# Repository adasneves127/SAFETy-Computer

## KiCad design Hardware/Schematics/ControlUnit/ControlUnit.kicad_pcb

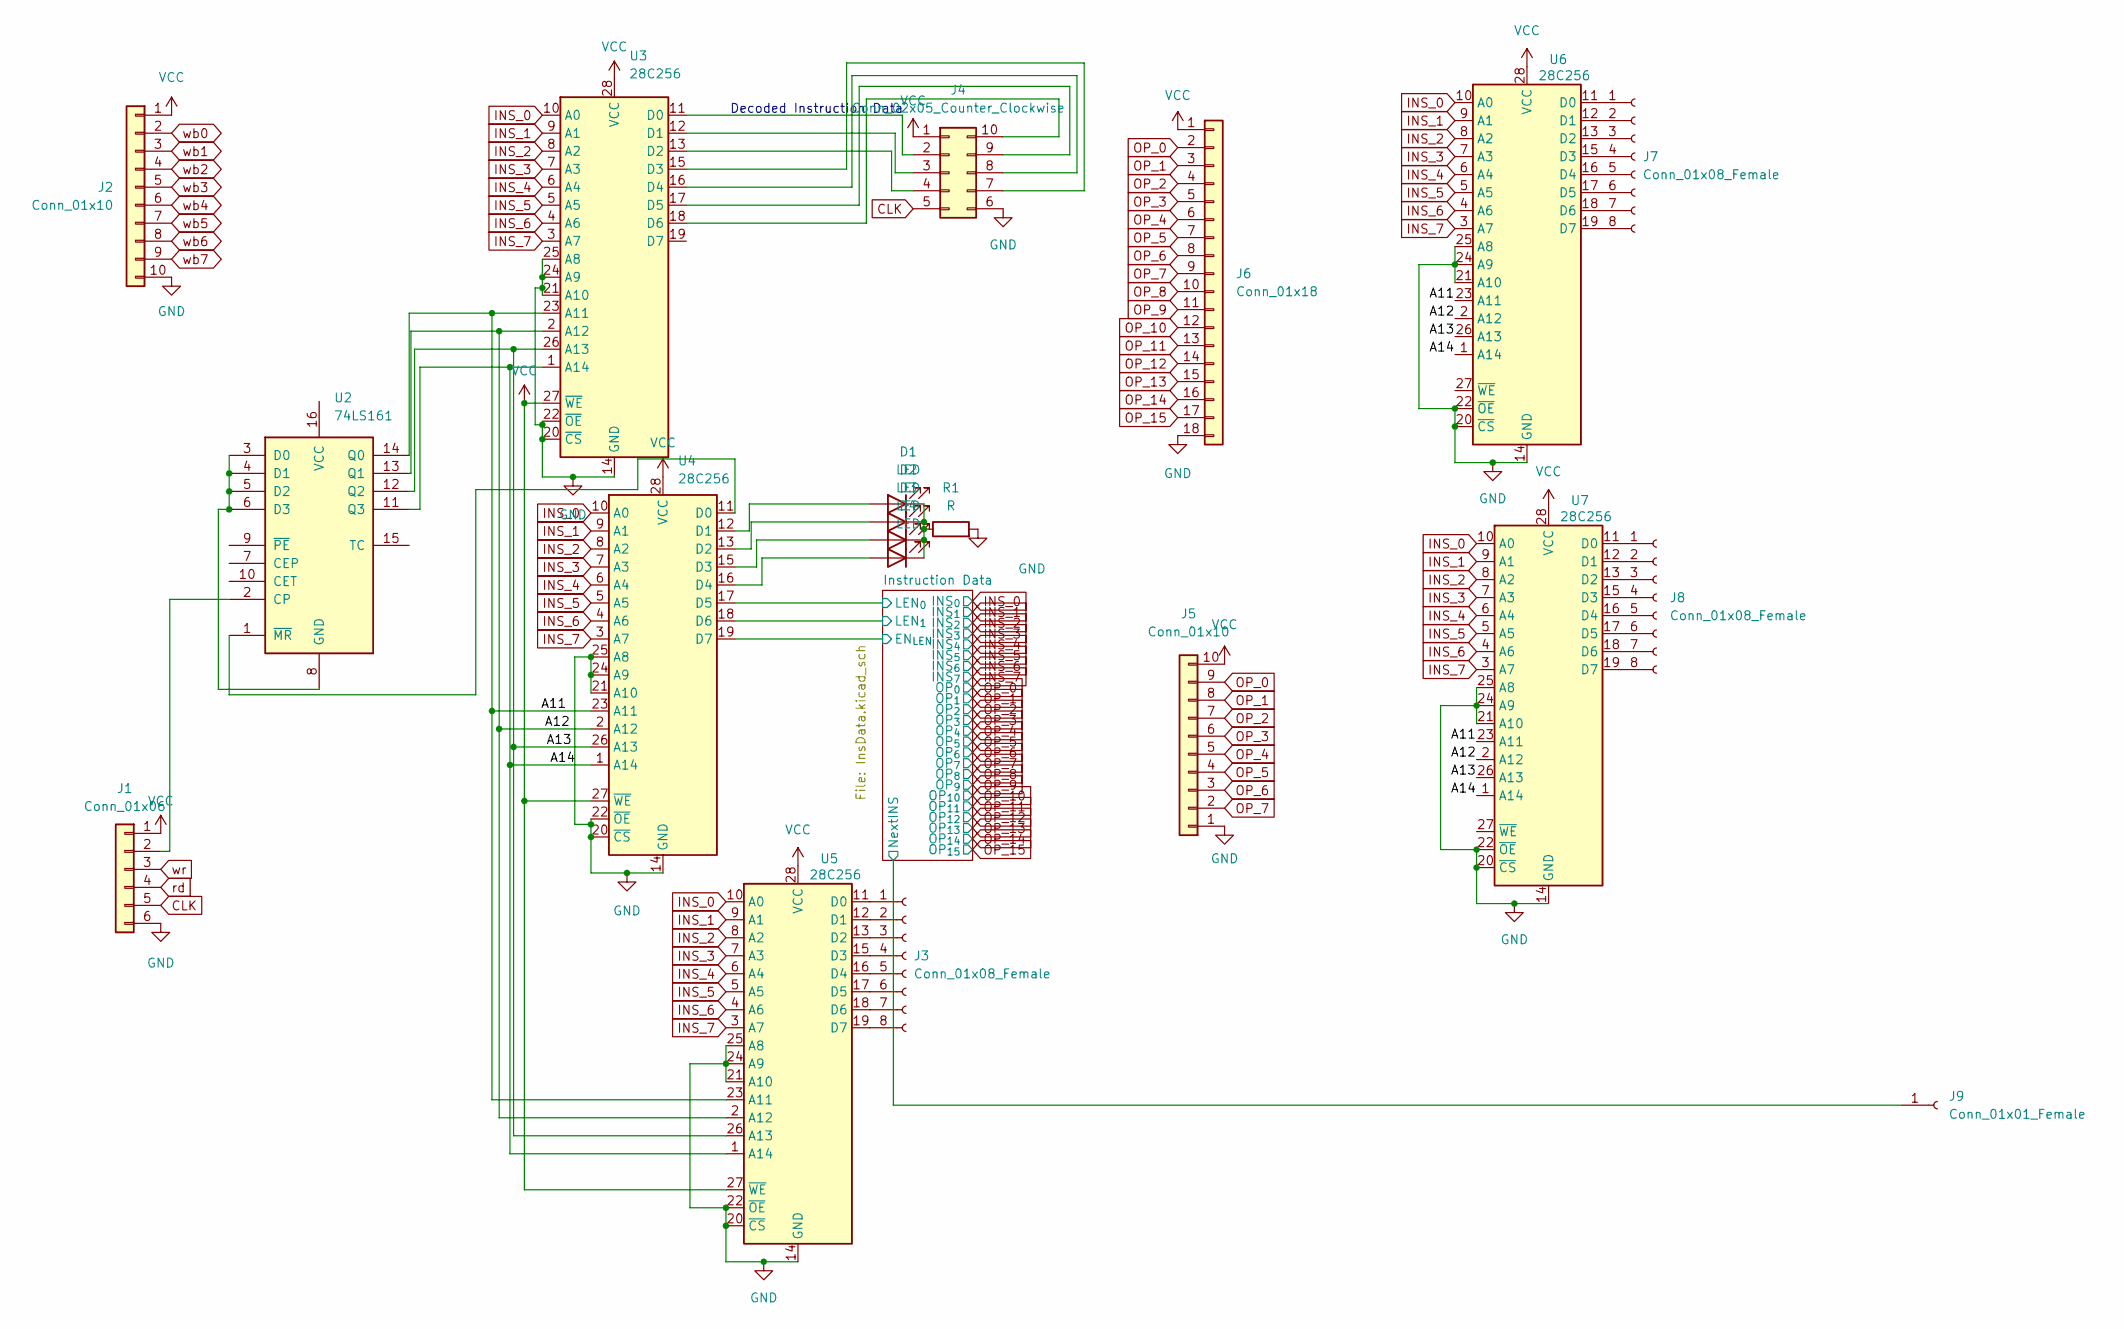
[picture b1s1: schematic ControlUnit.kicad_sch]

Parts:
D1, D2, D3, D4: LED; LED_D3.0mm
J1: Conn_01x06; PinSocket_1x06_P2.54mm_Vertical
J2, J5: Conn_01x10; PinHeader_1x10_P2.54mm_Vertical
J3, J7, J8: Conn_01x08_Female; PinSocket_1x08_P2.54mm_Vertical
J4: Conn_02x05_Counter_Clockwise; PinHeader_2x05_P2.54mm_Vertical
J6: Conn_01x18; PinSocket_1x18_P2.54mm_Vertical
J9: Conn_01x01_Female; PinSocket_1x01_P2.54mm_Horizontal
R1: R; R_Axial_DIN0204_L3.6mm_D1.6mm_P2.54mm_Vertical
U2: 74LS161; DIP-16_W7.62mm_Socket_LongPads
U3, U4, U5, U6, U7: 28C256; DIP-28_W15.24mm_Socket_LongPads

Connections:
/A11: U2.14 (Q0), U3.23 (A11), U4.23 (A11), U5.23 (A11), U6.23 (A11), U7.23 (A11)
/A12: U2.13 (Q1), U3.2 (A12), U4.2 (A12), U5.2 (A12), U6.2 (A12), U7.2 (A12)
/A13: U2.12 (Q2), U3.26 (A13), U4.26 (A13), U5.26 (A13), U6.26 (A13), U7.26 (A13)
/A14: U2.11 (Q3), U3.1 (A14), U4.1 (A14), U5.1 (A14), U6.1 (A14), U7.1 (A14)
/Instruction Data/EN_{LEN}: U4.19 (D7); also elsewhere on the board
/Instruction Data/LEN_{0}: U4.17 (D5); also elsewhere on the board
/Instruction Data/LEN_{1}: U4.18 (D6); also elsewhere on the board
/Instruction Data/NextINS: J9.1; also elsewhere on the board
CLK: J1.5, J4.5; also elsewhere on the board
GND: J1.6, J2.10, J4.6, J5.1, J6.18, R1.2, U3.14 (GND), U3.20 (~CS), U3.21 (A10), U3.22 (~OE), U3.24 (A9), U3.25 (A8), U4.14 (GND), U4.20 (~CS), U4.21 (A10), U4.22 (~OE), U4.24 (A9), U4.25 (A8), U5.14 (GND), U5.20 (~CS), U5.21 (A10), U5.22 (~OE), U5.24 (A9), U5.25 (A8), U6.14 (GND), U6.20 (~CS), U6.21 (A10), U6.22 (~OE), U6.24 (A9), U6.25 (A8), U7.14 (GND), U7.20 (~CS), U7.21 (A10), U7.22 (~OE), U7.24 (A9), U7.25 (A8); also elsewhere on the board
INS_0: U3.10 (A0), U4.10 (A0), U5.10 (A0), U6.10 (A0), U7.10 (A0); also elsewhere on the board
INS_1: U3.9 (A1), U4.9 (A1), U5.9 (A1), U6.9 (A1), U7.9 (A1); also elsewhere on the board
INS_2: U3.8 (A2), U4.8 (A2), U5.8 (A2), U6.8 (A2), U7.8 (A2); also elsewhere on the board
INS_3: U3.7 (A3), U4.7 (A3), U5.7 (A3), U6.7 (A3), U7.7 (A3); also elsewhere on the board
INS_4: U3.6 (A4), U4.6 (A4), U5.6 (A4), U6.6 (A4), U7.6 (A4); also elsewhere on the board
INS_5: U3.5 (A5), U4.5 (A5), U5.5 (A5), U6.5 (A5), U7.5 (A5); also elsewhere on the board
INS_6: U3.4 (A6), U4.4 (A6), U5.4 (A6), U6.4 (A6), U7.4 (A6); also elsewhere on the board
INS_7: U3.3 (A7), U4.3 (A7), U5.3 (A7), U6.3 (A7), U7.3 (A7); also elsewhere on the board
unnamed: D1.1 (K), D2.1 (K), D3.1 (K), D4.1 (K), R1.1
unnamed: D1.2 (A), U4.12 (D1)
unnamed: D2.2 (A), U4.13 (D2)
unnamed: D3.2 (A), U4.15 (D3)
unnamed: D4.2 (A), U4.16 (D4)
unnamed: J1.2, U2.2 (CP)
unnamed: J3.1, U5.11 (D0)
unnamed: J3.2, U5.12 (D1)
unnamed: J3.3, U5.13 (D2)
unnamed: J3.4, U5.15 (D3)
unnamed: J3.5, U5.16 (D4)
unnamed: J3.6, U5.17 (D5)
unnamed: J3.7, U5.18 (D6)
unnamed: J3.8, U5.19 (D7)
unnamed: J4.2, U3.11 (D0)
unnamed: J4.3, U3.12 (D1)
unnamed: J4.4, U3.13 (D2)
unnamed: J4.7, U3.15 (D3)
unnamed: J4.8, U3.16 (D4)
unnamed: J4.9, U3.17 (D5)
unnamed: J4.10, U3.18 (D6)
unnamed: J7.1, U6.11 (D0)
unnamed: J7.2, U6.12 (D1)
unnamed: J7.3, U6.13 (D2)
unnamed: J7.4, U6.15 (D3)
unnamed: J7.5, U6.16 (D4)
unnamed: J7.6, U6.17 (D5)
unnamed: J7.7, U6.18 (D6)
unnamed: J7.8, U6.19 (D7)
unnamed: J8.1, U7.11 (D0)
unnamed: J8.2, U7.12 (D1)
unnamed: J8.3, U7.13 (D2)
unnamed: J8.4, U7.15 (D3)
unnamed: J8.5, U7.16 (D4)
unnamed: J8.6, U7.17 (D5)
unnamed: J8.7, U7.18 (D6)
unnamed: J8.8, U7.19 (D7)
unnamed: U2.1 (~MR), U4.11 (D0)
unnamed: U2.3 (D0), U2.4 (D1), U2.5 (D2), U2.6 (D3), U2.8 (GND)
OP_0: J5.9, J6.2; also elsewhere on the board
OP_1: J5.8, J6.3; also elsewhere on the board
OP_2: J5.7, J6.4; also elsewhere on the board
OP_3: J5.6, J6.5; also elsewhere on the board
OP_4: J5.5, J6.6; also elsewhere on the board
OP_5: J5.4, J6.7; also elsewhere on the board
OP_6: J5.3, J6.8; also elsewhere on the board
OP_7: J5.2, J6.9; also elsewhere on the board
OP_8: J6.10; also elsewhere on the board
OP_9: J6.11; also elsewhere on the board
OP_10: J6.12; also elsewhere on the board
OP_11: J6.13; also elsewhere on the board
OP_12: J6.14; also elsewhere on the board
OP_13: J6.15; also elsewhere on the board
OP_14: J6.16; also elsewhere on the board
OP_15: J6.17; also elsewhere on the board
VCC: J1.1, J2.1, J4.1, J5.10, J6.1, U3.27 (~WE), U3.28 (VCC), U4.27 (~WE), U4.28 (VCC), U5.27 (~WE), U5.28 (VCC), U6.28 (VCC), U7.28 (VCC); also elsewhere on the board
rd: J1.4
wb0: J2.2; also elsewhere on the board
wb1: J2.3; also elsewhere on the board
wb2: J2.4; also elsewhere on the board
wb3: J2.5; also elsewhere on the board
wb4: J2.6; also elsewhere on the board
wb5: J2.7; also elsewhere on the board
wb6: J2.8; also elsewhere on the board
wb7: J2.9; also elsewhere on the board
wr: J1.3

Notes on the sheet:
Decoded Instruction Data

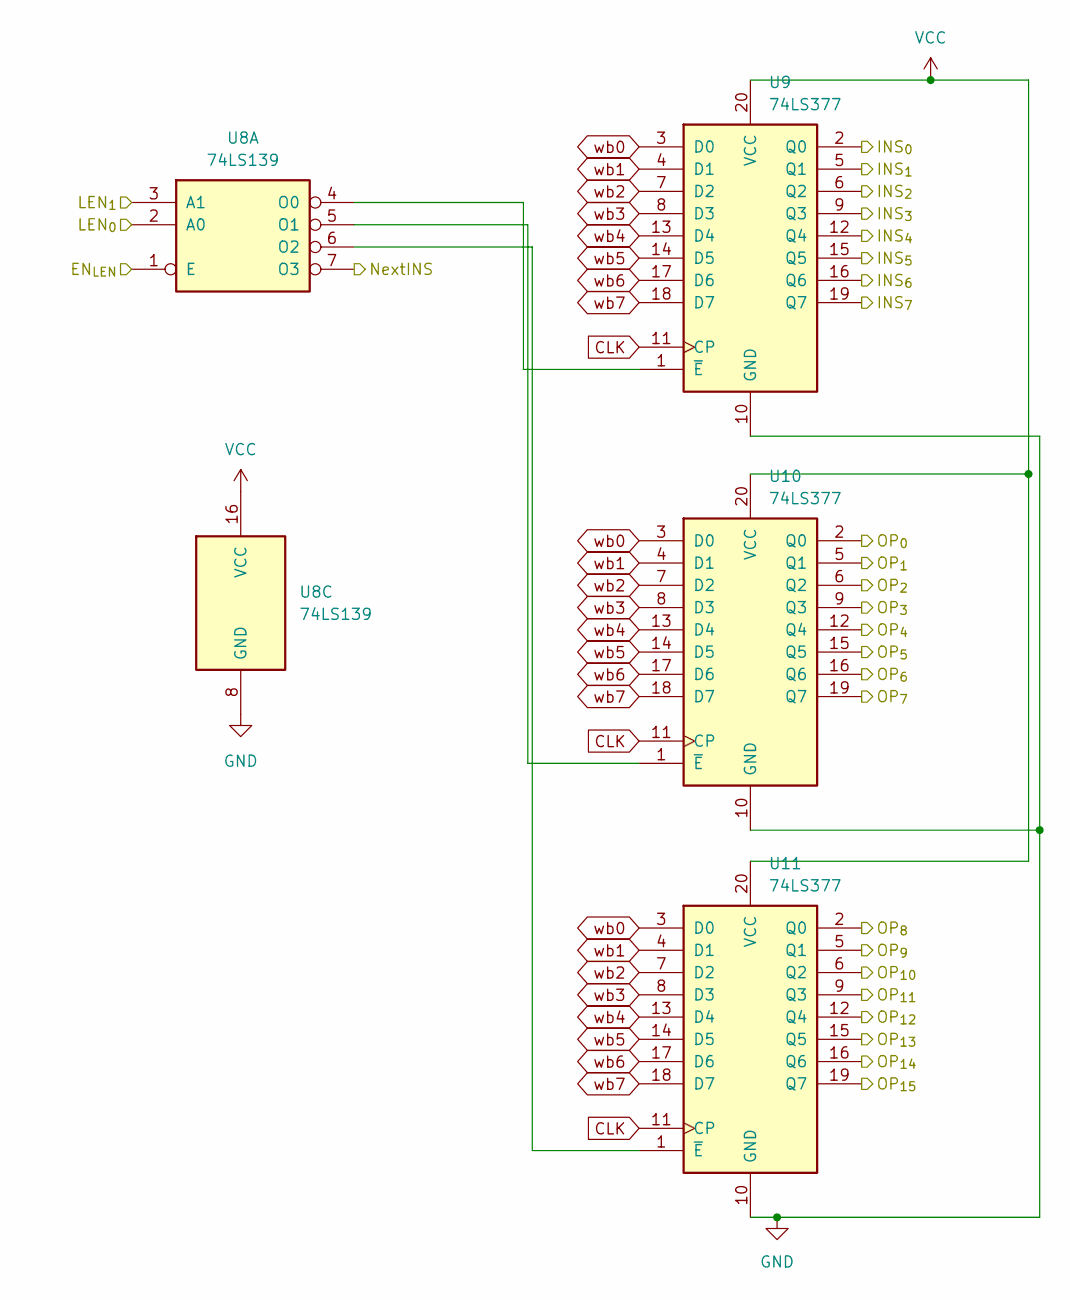
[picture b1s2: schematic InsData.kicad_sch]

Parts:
U8: 74LS139; DIP-16_W7.62mm_Socket_LongPads
U9, U10, U11: 74LS377; DIP-20_W7.62mm_Socket_LongPads

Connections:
/Instruction Data/EN_{LEN}: U8.1 (E); also elsewhere on the board
/Instruction Data/LEN_{0}: U8.2 (A0); also elsewhere on the board
/Instruction Data/LEN_{1}: U8.3 (A1); also elsewhere on the board
/Instruction Data/NextINS: U8.7 (O3); also elsewhere on the board
CLK: U9.11 (CP), U10.11 (CP), U11.11 (CP); also elsewhere on the board
GND: U8.8 (GND), U9.10 (GND), U10.10 (GND), U11.10 (GND); also elsewhere on the board
INS_0: U9.2 (Q0); also elsewhere on the board
INS_1: U9.5 (Q1); also elsewhere on the board
INS_2: U9.6 (Q2); also elsewhere on the board
INS_3: U9.9 (Q3); also elsewhere on the board
INS_4: U9.12 (Q4); also elsewhere on the board
INS_5: U9.15 (Q5); also elsewhere on the board
INS_6: U9.16 (Q6); also elsewhere on the board
INS_7: U9.19 (Q7); also elsewhere on the board
unnamed: U8.4 (O0), U9.1 (~E)
unnamed: U8.5 (O1), U10.1 (~E)
unnamed: U8.6 (O2), U11.1 (~E)
OP_0: U10.2 (Q0); also elsewhere on the board
OP_1: U10.5 (Q1); also elsewhere on the board
OP_2: U10.6 (Q2); also elsewhere on the board
OP_3: U10.9 (Q3); also elsewhere on the board
OP_4: U10.12 (Q4); also elsewhere on the board
OP_5: U10.15 (Q5); also elsewhere on the board
OP_6: U10.16 (Q6); also elsewhere on the board
OP_7: U10.19 (Q7); also elsewhere on the board
OP_8: U11.2 (Q0); also elsewhere on the board
OP_9: U11.5 (Q1); also elsewhere on the board
OP_10: U11.6 (Q2); also elsewhere on the board
OP_11: U11.9 (Q3); also elsewhere on the board
OP_12: U11.12 (Q4); also elsewhere on the board
OP_13: U11.15 (Q5); also elsewhere on the board
OP_14: U11.16 (Q6); also elsewhere on the board
OP_15: U11.19 (Q7); also elsewhere on the board
VCC: U8.16 (VCC), U9.20 (VCC), U10.20 (VCC), U11.20 (VCC); also elsewhere on the board
wb0: U9.3 (D0), U10.3 (D0), U11.3 (D0); also elsewhere on the board
wb1: U9.4 (D1), U10.4 (D1), U11.4 (D1); also elsewhere on the board
wb2: U9.7 (D2), U10.7 (D2), U11.7 (D2); also elsewhere on the board
wb3: U9.8 (D3), U10.8 (D3), U11.8 (D3); also elsewhere on the board
wb4: U9.13 (D4), U10.13 (D4), U11.13 (D4); also elsewhere on the board
wb5: U9.14 (D5), U10.14 (D5), U11.14 (D5); also elsewhere on the board
wb6: U9.17 (D6), U10.17 (D6), U11.17 (D6); also elsewhere on the board
wb7: U9.18 (D7), U10.18 (D7), U11.18 (D7); also elsewhere on the board

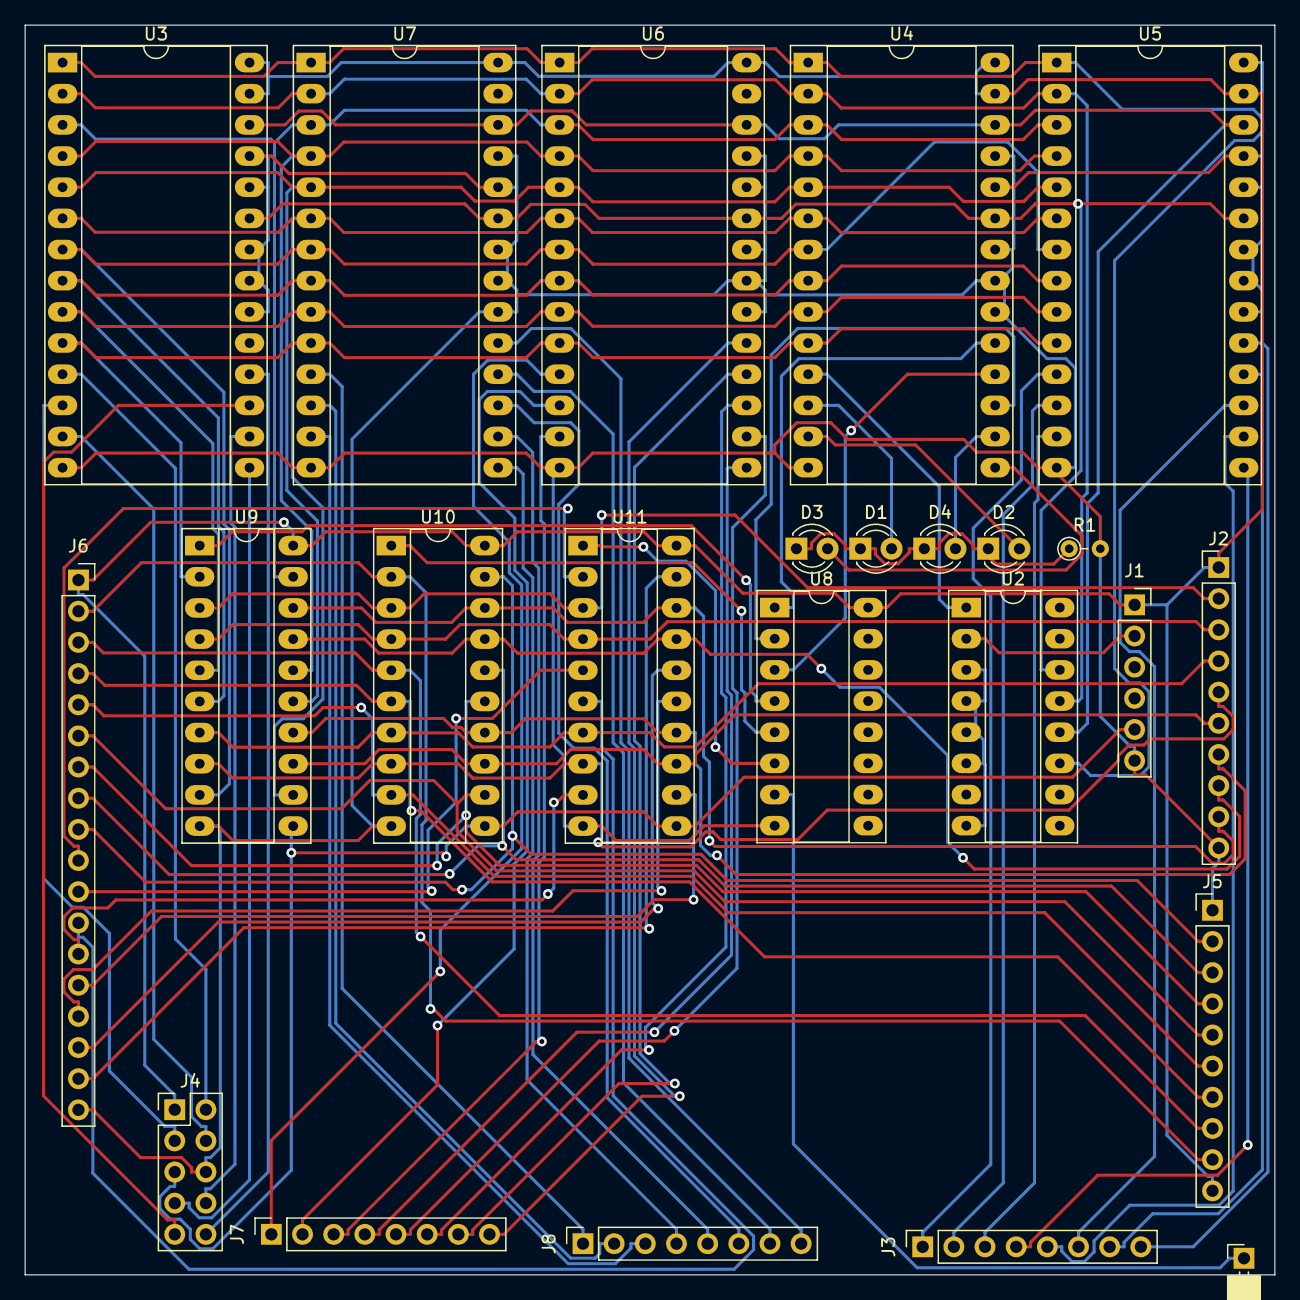
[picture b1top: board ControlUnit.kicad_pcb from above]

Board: 2 copper layers, 101.9 x 101.9 mm, 24 parts (0 on the bottom side), 85 nets.

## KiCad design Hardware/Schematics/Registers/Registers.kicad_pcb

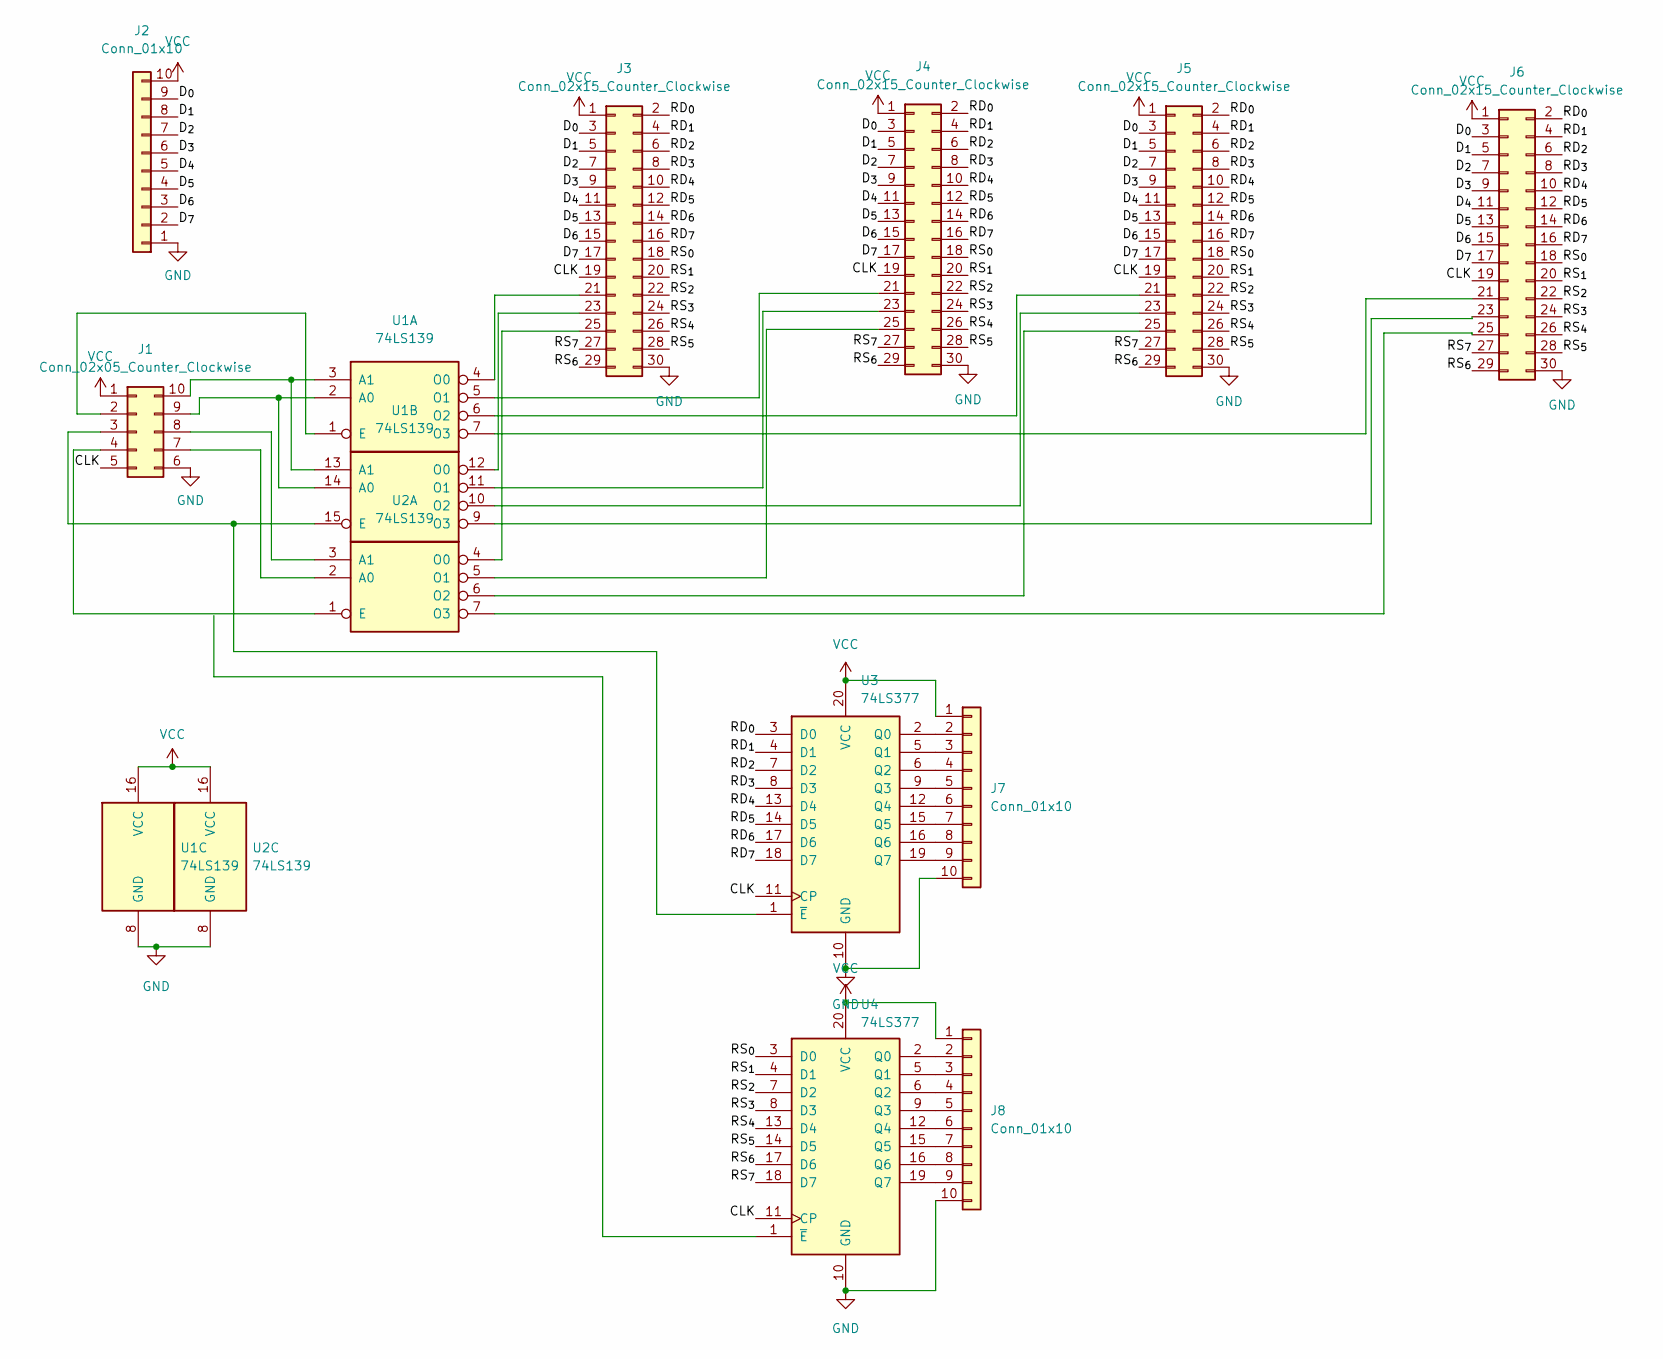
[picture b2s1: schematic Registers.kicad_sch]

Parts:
J1: Conn_02x05_Counter_Clockwise; PinHeader_2x05_P2.54mm_Vertical
J2, J7, J8: Conn_01x10; PinHeader_1x10_P2.54mm_Vertical
J3, J4, J5, J6: Conn_02x15_Counter_Clockwise; PinHeader_2x15_P2.54mm_Vertical
U1, U2: 74LS139; DIP-16_W7.62mm_Socket_LongPads
U3, U4: 74LS377; DIP-20_W7.62mm_Socket_LongPads

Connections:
/CLK: J1.5, J3.19, J4.19, J5.19, J6.19, U3.11 (CP), U4.11 (CP)
/D_{0}: J2.9, J3.3, J4.3, J5.3, J6.3
/D_{1}: J2.8, J3.5, J4.5, J5.5, J6.5
/D_{2}: J2.7, J3.7, J4.7, J5.7, J6.7
/D_{3}: J2.6, J3.9, J4.9, J5.9, J6.9
/D_{4}: J2.5, J3.11, J4.11, J5.11, J6.11
/D_{5}: J2.4, J3.13, J4.13, J5.13, J6.13
/D_{6}: J2.3, J3.15, J4.15, J5.15, J6.15
/D_{7}: J2.2, J3.17, J4.17, J5.17, J6.17
/RD_{0}: J3.2, J4.2, J5.2, J6.2, U3.3 (D0)
/RD_{1}: J3.4, J4.4, J5.4, J6.4, U3.4 (D1)
/RD_{2}: J3.6, J4.6, J5.6, J6.6, U3.7 (D2)
/RD_{3}: J3.8, J4.8, J5.8, J6.8, U3.8 (D3)
/RD_{4}: J3.10, J4.10, J5.10, J6.10, U3.13 (D4)
/RD_{5}: J3.12, J4.12, J5.12, J6.12, U3.14 (D5)
/RD_{6}: J3.14, J4.14, J5.14, J6.14, U3.17 (D6)
/RD_{7}: J3.16, J4.16, J5.16, J6.16, U3.18 (D7)
/RS_{0}: J3.18, J4.18, J5.18, J6.18, U4.3 (D0)
/RS_{1}: J3.20, J4.20, J5.20, J6.20, U4.4 (D1)
/RS_{2}: J3.22, J4.22, J5.22, J6.22, U4.7 (D2)
/RS_{3}: J3.24, J4.24, J5.24, J6.24, U4.8 (D3)
/RS_{4}: J3.26, J4.26, J5.26, J6.26, U4.13 (D4)
/RS_{5}: J3.28, J4.28, J5.28, J6.28, U4.14 (D5)
/RS_{6}: J3.29, J4.29, J5.29, J6.29, U4.17 (D6)
/RS_{7}: J3.27, J4.27, J5.27, J6.27, U4.18 (D7)
GND: J1.6, J2.1, J3.30, J4.30, J5.30, J6.30, J7.10, J8.10, U1.8 (GND), U2.8 (GND), U3.10 (GND), U4.10 (GND)
unnamed: J1.2, U1.1 (E)
unnamed: J1.3, U1.15 (E), U3.1 (~E)
unnamed: J1.4, U2.1 (E)
unnamed: J1.7, U2.2 (A0)
unnamed: J1.8, U2.3 (A1)
unnamed: J1.9, U1.2 (A0), U1.14 (A0)
unnamed: J1.10, U1.3 (A1), U1.13 (A1)
unnamed: J3.21, U1.4 (O0)
unnamed: J3.23, U1.12 (O0)
unnamed: J3.25, U2.4 (O0)
unnamed: J4.21, U1.5 (O1)
unnamed: J4.23, U1.11 (O1)
unnamed: J4.25, U2.5 (O1)
unnamed: J5.21, U1.6 (O2)
unnamed: J5.23, U1.10 (O2)
unnamed: J5.25, U2.6 (O2)
unnamed: J6.21, U1.7 (O3)
unnamed: J6.23, U1.9 (O3)
unnamed: J6.25, U2.7 (O3)
unnamed: J7.2, U3.2 (Q0)
unnamed: J7.3, U3.5 (Q1)
unnamed: J7.4, U3.6 (Q2)
unnamed: J7.5, U3.9 (Q3)
unnamed: J7.6, U3.12 (Q4)
unnamed: J7.7, U3.15 (Q5)
unnamed: J7.8, U3.16 (Q6)
unnamed: J7.9, U3.19 (Q7)
unnamed: J8.2, U4.2 (Q0)
unnamed: J8.3, U4.5 (Q1)
unnamed: J8.4, U4.6 (Q2)
unnamed: J8.5, U4.9 (Q3)
unnamed: J8.6, U4.12 (Q4)
unnamed: J8.7, U4.15 (Q5)
unnamed: J8.8, U4.16 (Q6)
unnamed: J8.9, U4.19 (Q7)
VCC: J1.1, J2.10, J3.1, J4.1, J5.1, J6.1, J7.1, J8.1, U1.16 (VCC), U2.16 (VCC), U3.20 (VCC), U4.20 (VCC)

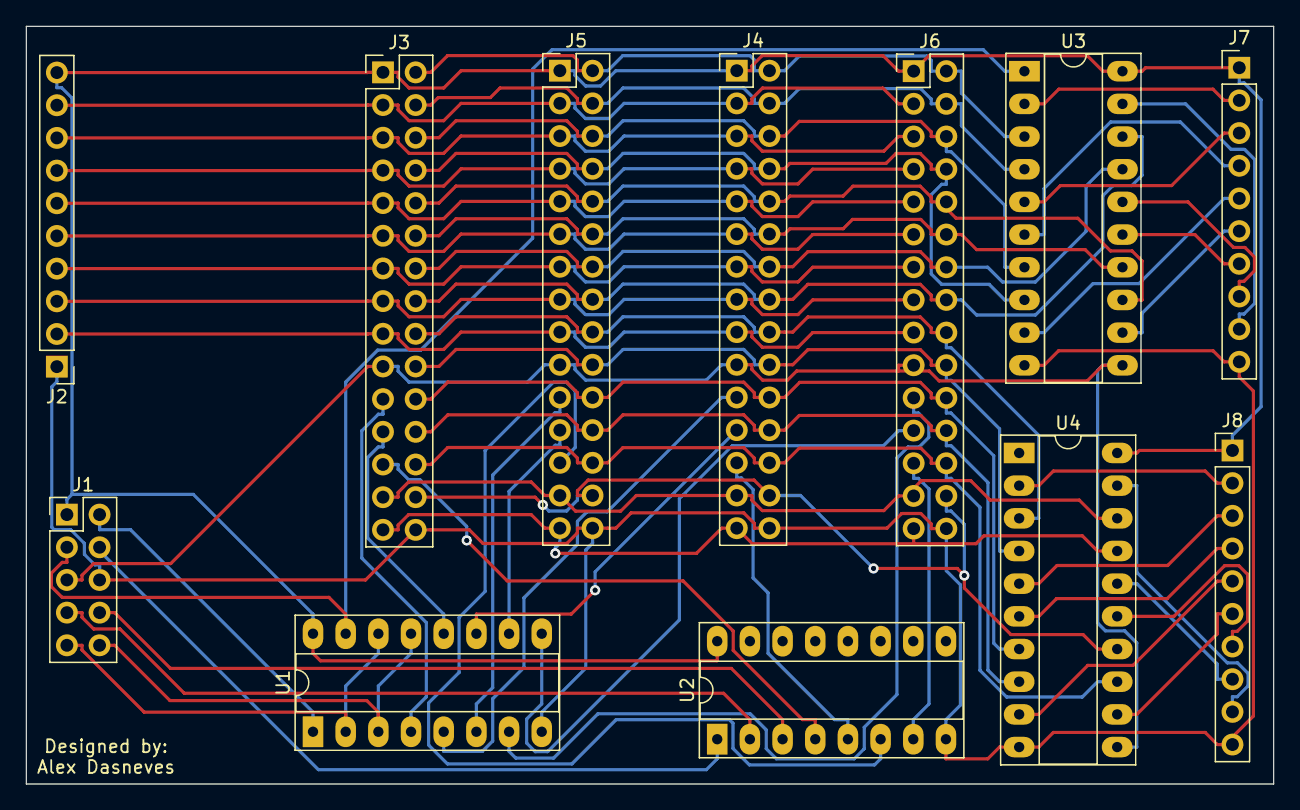
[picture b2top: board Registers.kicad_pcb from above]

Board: 2 copper layers, 96.9 x 58.9 mm, 12 parts (0 on the bottom side), 62 nets.

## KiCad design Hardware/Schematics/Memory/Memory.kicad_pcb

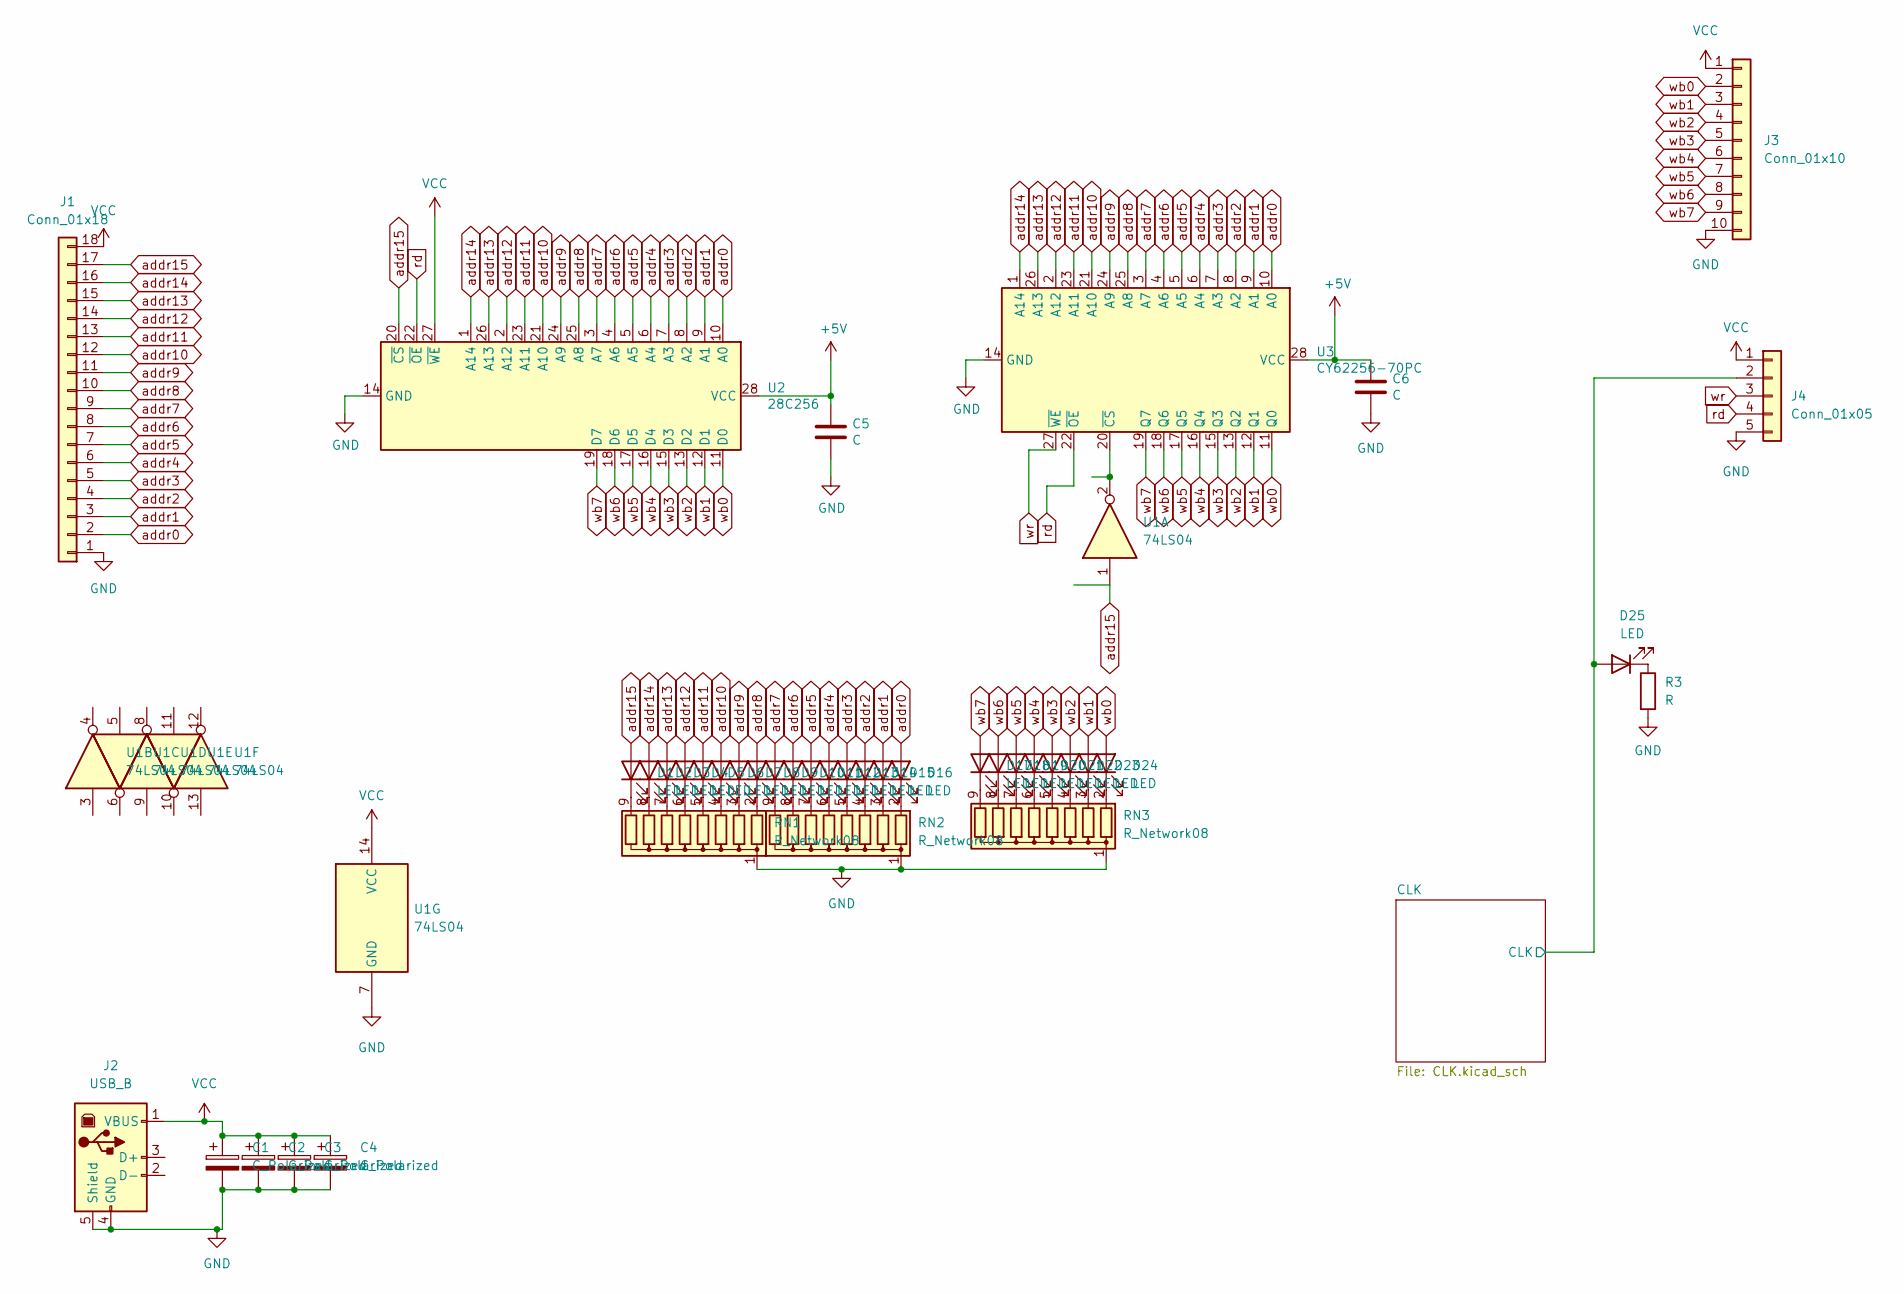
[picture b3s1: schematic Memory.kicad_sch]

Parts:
C1, C2, C3, C4: C_Polarized; CP_Radial_D8.0mm_P3.80mm
C5, C6: C; C_Disc_D3.0mm_W2.0mm_P2.50mm
D1, D2, D3, D4, D5, D6, D7, D8, D9, D10, D11, D12, D13, D14, D15, D16, D17, D18, D19, D20, D21, D22, D23, D24, D25: LED; LED_D3.0mm
J1: Conn_01x18; PinHeader_1x18_P2.54mm_Vertical
J2: USB_B; USB_B_Lumberg_2411_02_Horizontal
J3: Conn_01x10; PinHeader_1x10_P2.54mm_Vertical
J4: Conn_01x05; PinHeader_1x05_P2.54mm_Vertical
R3: R; R_Axial_DIN0204_L3.6mm_D1.6mm_P2.54mm_Vertical
RN1, RN2, RN3: R_Network08; R_Array_SIP9
U1: 74LS04; DIP-14_W7.62mm_Socket_LongPads
U2: 28C256; DIP-28_W15.24mm
U3: CY62256-70PC; DIP-28_W15.24mm

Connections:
+5V: C5.1, C6.1, U2.28 (VCC), U3.28 (VCC)
/CLK/CLK: D25.2 (A), J4.2; also elsewhere on the board
GND: C1.2, C2.2, C3.2, C4.2, C5.2, C6.2, J1.1, J2.4 (GND), J2.5 (Shield), J3.10, J4.5, R3.2, RN1.1 (common), RN2.1 (common), RN3.1 (common), U1.7 (GND), U2.14 (GND), U3.14 (GND); also elsewhere on the board
unnamed: D1.1 (K), RN1.9 (R8)
unnamed: D2.1 (K), RN1.8 (R7)
unnamed: D3.1 (K), RN1.7 (R6)
unnamed: D4.1 (K), RN1.6 (R5)
unnamed: D5.1 (K), RN1.5 (R4)
unnamed: D6.1 (K), RN1.4 (R3)
unnamed: D7.1 (K), RN1.3 (R2)
unnamed: D8.1 (K), RN1.2 (R1)
unnamed: D9.1 (K), RN2.9 (R8)
unnamed: D10.1 (K), RN2.8 (R7)
unnamed: D11.1 (K), RN2.7 (R6)
unnamed: D12.1 (K), RN2.6 (R5)
unnamed: D13.1 (K), RN2.5 (R4)
unnamed: D14.1 (K), RN2.4 (R3)
unnamed: D15.1 (K), RN2.3 (R2)
unnamed: D16.1 (K), RN2.2 (R1)
unnamed: D17.1 (K), RN3.9 (R8)
unnamed: D18.1 (K), RN3.8 (R7)
unnamed: D19.1 (K), RN3.7 (R6)
unnamed: D20.1 (K), RN3.6 (R5)
unnamed: D21.1 (K), RN3.5 (R4)
unnamed: D22.1 (K), RN3.4 (R3)
unnamed: D23.1 (K), RN3.3 (R2)
unnamed: D24.1 (K), RN3.2 (R1)
unnamed: D25.1 (K), R3.1
unnamed: U1.2, U3.20 (~CS)
VCC: C1.1, C2.1, C3.1, C4.1, J1.18, J2.1 (VBUS), J3.1, J4.1, U1.14 (VCC), U2.27 (~WE); also elsewhere on the board
addr0: D16.2 (A), J1.2, U2.10 (A0), U3.10 (A0)
addr1: D15.2 (A), J1.3, U2.9 (A1), U3.9 (A1)
addr2: D14.2 (A), J1.4, U2.8 (A2), U3.8 (A2)
addr3: D13.2 (A), J1.5, U2.7 (A3), U3.7 (A3)
addr4: D12.2 (A), J1.6, U2.6 (A4), U3.6 (A4)
addr5: D11.2 (A), J1.7, U2.5 (A5), U3.5 (A5)
addr6: D10.2 (A), J1.8, U2.4 (A6), U3.4 (A6)
addr7: D9.2 (A), J1.9, U2.3 (A7), U3.3 (A7)
addr8: D8.2 (A), J1.10, U2.25 (A8), U3.25 (A8)
addr9: D7.2 (A), J1.11, U2.24 (A9), U3.24 (A9)
addr10: D6.2 (A), J1.12, U2.21 (A10), U3.21 (A10)
addr11: D5.2 (A), J1.13, U2.23 (A11), U3.23 (A11)
addr12: D4.2 (A), J1.14, U2.2 (A12), U3.2 (A12)
addr13: D3.2 (A), J1.15, U2.26 (A13), U3.26 (A13)
addr14: D2.2 (A), J1.16, U2.1 (A14), U3.1 (A14)
addr15: D1.2 (A), J1.17, U1.1, U2.20 (~CS)
rd: J4.4, U2.22 (~OE), U3.22 (~OE)
wb0: D24.2 (A), J3.2, U2.11 (D0), U3.11 (Q0)
wb1: D23.2 (A), J3.3, U2.12 (D1), U3.12 (Q1)
wb2: D22.2 (A), J3.4, U2.13 (D2), U3.13 (Q2)
wb3: D21.2 (A), J3.5, U2.15 (D3), U3.15 (Q3)
wb4: D20.2 (A), J3.6, U2.16 (D4), U3.16 (Q4)
wb5: D19.2 (A), J3.7, U2.17 (D5), U3.17 (Q5)
wb6: D18.2 (A), J3.8, U2.18 (D6), U3.18 (Q6)
wb7: D17.2 (A), J3.9, U2.19 (D7), U3.19 (Q7)
wr: J4.3, U3.27 (~WE)

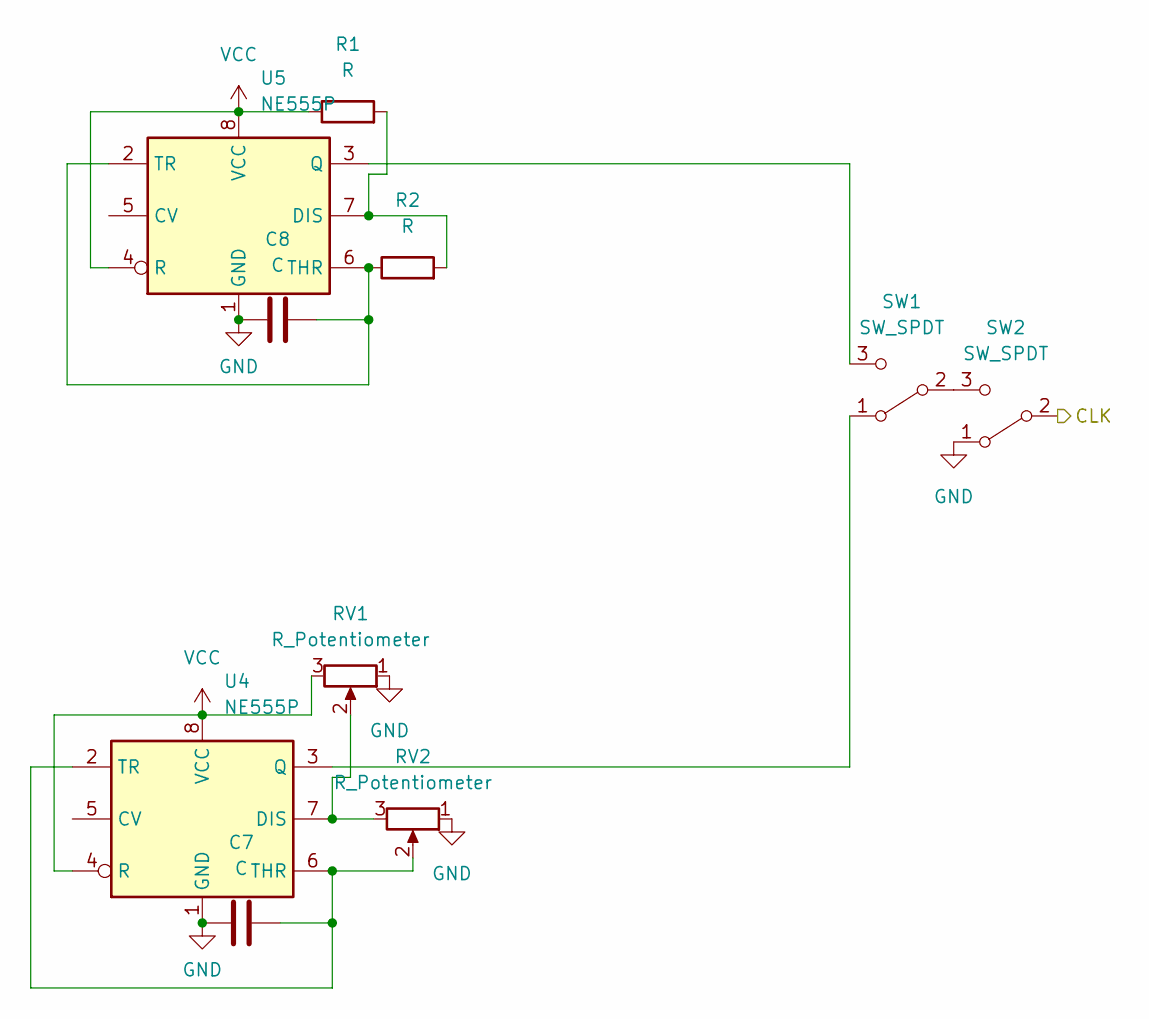
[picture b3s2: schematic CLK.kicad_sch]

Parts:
C7, C8: C; C_Disc_D3.0mm_W2.0mm_P2.50mm
R1, R2: R; R_Axial_DIN0204_L3.6mm_D1.6mm_P2.54mm_Vertical
RV1, RV2: R_Potentiometer; Potentiometer_ACP_CA9-V10_Vertical
SW1, SW2: SW_SPDT; SW_CuK_OS102011MA1QN1_SPDT_Angled
U4, U5: NE555P; DIP-8_W7.62mm

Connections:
/CLK/CLK: SW2.2 (B); also elsewhere on the board
GND: C7.1, C8.1, RV1.1, RV2.1, SW2.1 (A), U4.1 (GND), U5.1 (GND); also elsewhere on the board
unnamed: C7.2, RV2.2, U4.2 (TR), U4.6 (THR)
unnamed: C8.2, R2.1, U5.2 (TR), U5.6 (THR)
unnamed: R1.2, R2.2, U5.7 (DIS)
unnamed: RV1.2, RV2.3, U4.7 (DIS)
unnamed: SW1.1 (A), U4.3 (Q)
unnamed: SW1.2 (B), SW2.3 (C)
unnamed: SW1.3 (C), U5.3 (Q)
VCC: R1.1, RV1.3, U4.4 (R), U4.8 (VCC), U5.4 (R), U5.8 (VCC); also elsewhere on the board

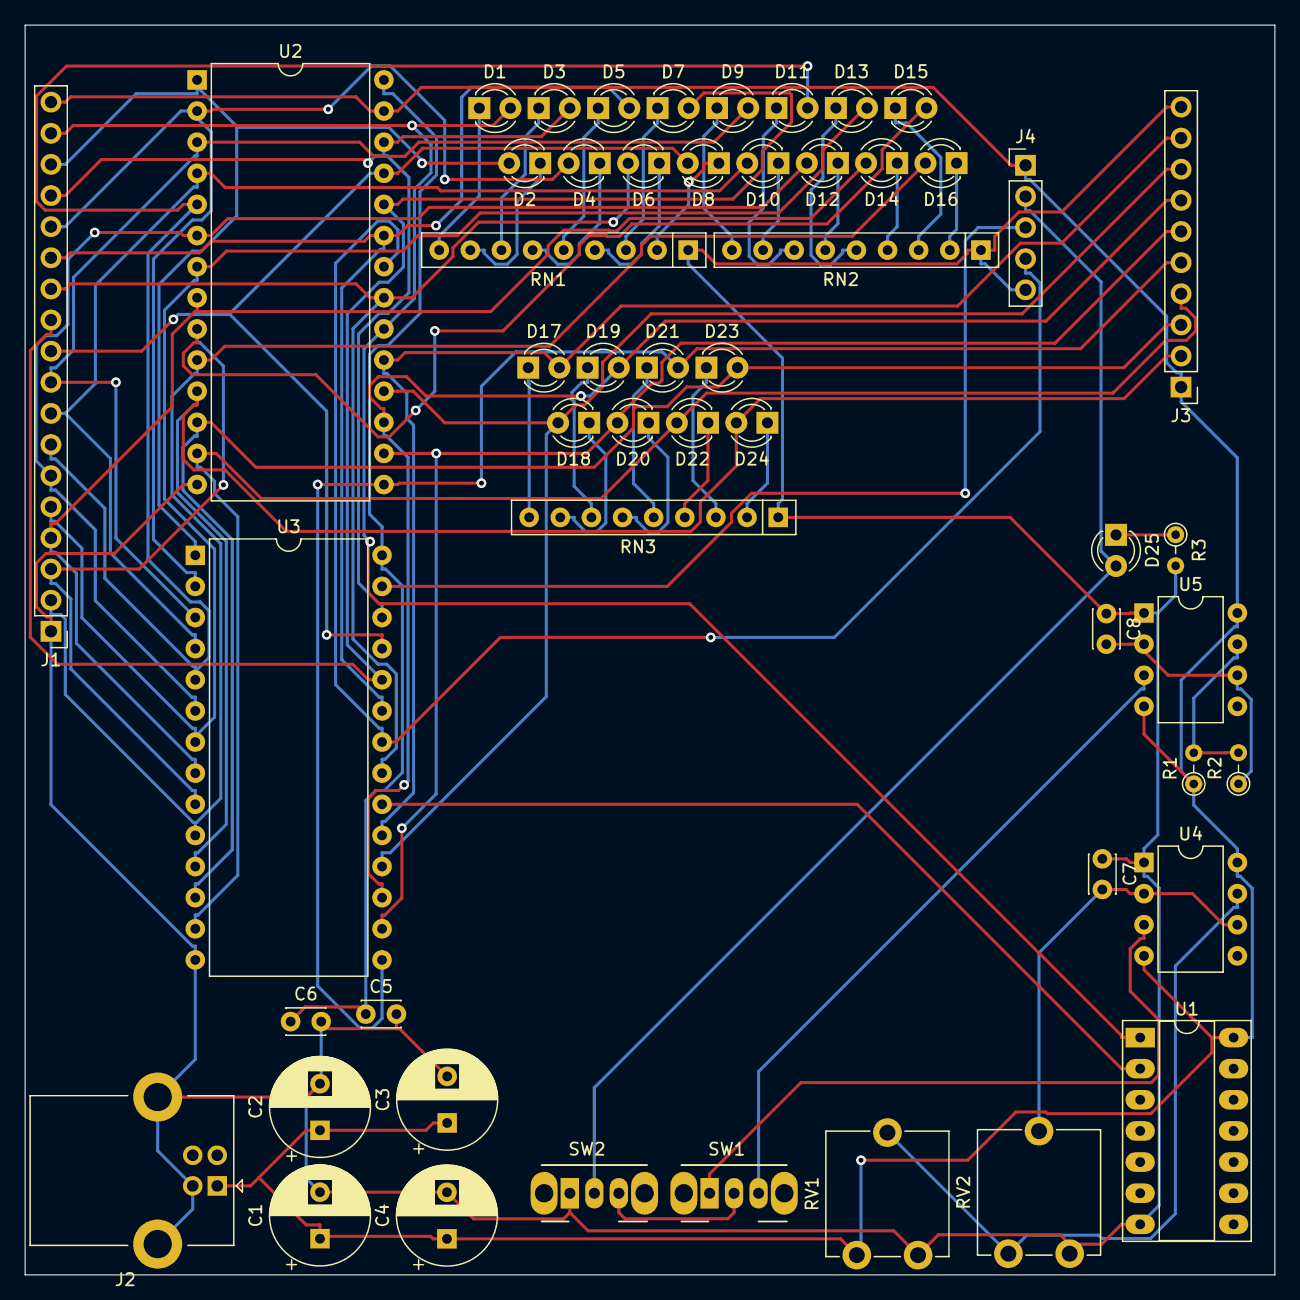
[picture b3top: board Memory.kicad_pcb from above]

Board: 2 copper layers, 102.0 x 102.0 mm, 52 parts (0 on the bottom side), 63 nets.
